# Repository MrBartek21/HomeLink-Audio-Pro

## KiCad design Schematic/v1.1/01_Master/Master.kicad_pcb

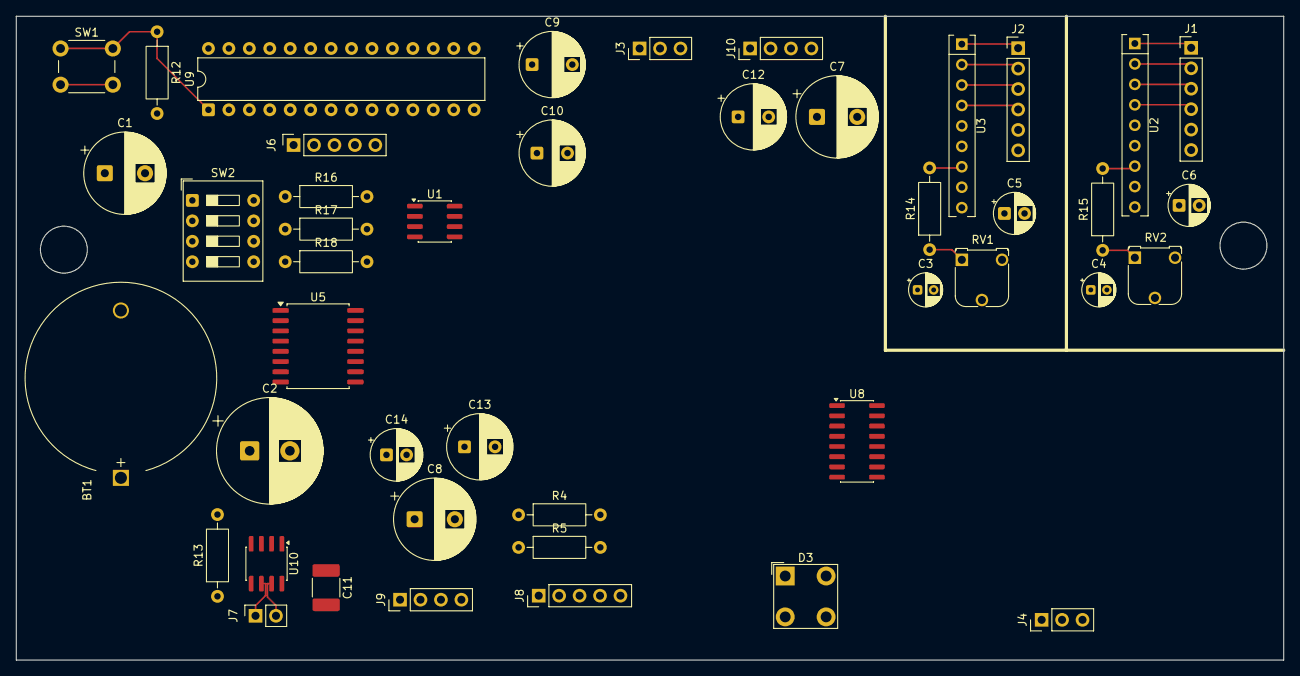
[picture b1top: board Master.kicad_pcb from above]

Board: 2 copper layers, 157.5 x 80.0 mm, 45 parts (0 on the bottom side), 40 nets.

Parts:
BT1: Battery; BatteryHolder_MYOUNG_BS-07-A1BJ001_CR2032
C1: 6.3v 3300uF; CP_Radial_D10.0mm_P5.00mm
C2: 35v 1000uF; CP_Radial_D13.0mm_P5.00mm
C3, C4: 16V 2.2uF; CP_Radial_D4.0mm_P2.00mm
C5, C6: 16V 10uF; CP_Radial_D5.0mm_P2.50mm
C7, C8: 6.3V 1500uF; CP_Radial_D10.0mm_P5.00mm
C9: 6.3V 1800uF; CP_Radial_D8.0mm_P5.00mm
C10: 6.3V 220uF; CP_Radial_D8.0mm_P3.80mm
C11: 100nF; C_1812_4532Metric_Pad1.57x3.40mm_HandSolder
C12: 10V 1000uF; CP_Radial_D8.0mm_P3.80mm
C13: 6.3V 1000uF; CP_Radial_D8.0mm_P3.80mm
C14: 16V 100uF; CP_Radial_D6.3mm_P2.50mm
D3: LED_Dual_AAKK; LED_BL-FL7680RGB
J1, J2: Conn_01x06_Pin; PinHeader_1x06_P2.54mm_Vertical
J3: BTN/LED; PinHeader_1x03_P2.54mm_Vertical
J4: AUDIO; PinHeader_1x03_P2.54mm_Vertical
J6: ISP; PinSocket_1x05_P2.54mm_Vertical
J7: RS-485; PinSocket_1x02_P2.54mm_Vertical
J8: IO/I2C; PinHeader_1x05_P2.54mm_Vertical
J9: POWER; PinHeader_1x04_P2.54mm_Vertical
J10: I2C; PinHeader_1x04_P2.54mm_Vertical
R4, R5: 4.7K; R_Axial_DIN0207_L6.3mm_D2.5mm_P10.16mm_Horizontal
R12, R14, R15: 10K; R_Axial_DIN0207_L6.3mm_D2.5mm_P10.16mm_Horizontal
R13: 5.1K; R_Axial_DIN0207_L6.3mm_D2.5mm_P10.16mm_Horizontal
R16, R17, R18: 1K; R_Axial_DIN0207_L6.3mm_D2.5mm_P10.16mm_Horizontal
RV1, RV2: 10K; Potentiometer_Runtron_RM-065_Vertical
SW1: SW_Push; SW_PUSH_6mm
SW2: SW_DIP_x04; SW_DIP_SPSTx04_Slide_9.78x12.34mm_W7.62mm_P2.54mm
U1: M24C02-FMN; SOIC-8_3.9x4.9mm_P1.27mm
U2, U3: KA2284; SIP-9_22.3x3mm_P2.54mm
U5: DS3231M; SOIC-16W_7.5x10.3mm_P1.27mm
U8: CH340C; SOIC-16_3.9x9.9mm_P1.27mm
U9: ATmega328-P; DIP-28_W7.62mm
U10: MAX485E; SOIC-8_3.9x4.9mm_P1.27mm

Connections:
+5V: C1.1, C2.1, C8.1, C9.1, C10.1, C11.1, C13.1, C14.1, J1.6, J2.6, J9.3, R4.1, R5.1, R12.2, R15.1, RV2.1, SW2.1, SW2.2, SW2.3, SW2.4, U1.8 (VCC), U2.9 (VCC), U3.9 (VCC), U5.2 (VCC), U9.7 (VCC), U9.20 (AVCC), U10.8 (VCC)
/Master/MISO: J6.4, U9.18 (PB4)
/Master/MOSI: J6.3, U9.17 (PB3)
/Master/SCK: J6.5, U9.19 (PB5)
/MultiMax/RS485-A-P: J7.1, U10.6 (A)
/MultiMax/RS485-B-N: J7.2, U10.7 (B)
ACS: J8.1, U9.23 (PC0)
ACTIVITY_ATMEGA8: D3.1 (A1), J8.2
ACTIVITY_ATMEGA328: D3.2 (A2), U9.6 (PD4)
AUDIO_L: C3.2, J4.1
AUDIO_R: C4.2, J4.3
DE_RE: R13.2, U9.14 (PB0), U10.2 (~RE), U10.3 (DE)
GND: BT1.2 (-), C1.2, C2.2, C5.2, C6.2, C7.2, C8.2, C9.2, C10.2, C11.2, C12.2, C13.2, C14.2, D3.3 (K1), D3.4 (K2), J4.2, J6.1, J8.3, J9.1, J9.2, J10.1, R13.1, R14.1, R16.1, R17.1, R18.1, RV1.1, SW1.2, U1.4 (VSS), U2.5 (GND), U3.5 (GND), U5.5 (GND), U5.6 (GND), U5.7 (GND), U5.8 (GND), U5.9 (GND), U5.10 (GND), U5.11 (GND), U5.12 (GND), U5.13 (GND), U9.8 (GND), U9.22 (GND), U10.5 (GND)
unnamed: BT1.1 (+), U5.14 (VBAT)
unnamed: C3.1, RV1.3
unnamed: C4.1, RV2.3
unnamed: J1.1, U2.1 (D1)
unnamed: J1.2, U2.2 (D2)
unnamed: J1.3, U2.3 (D3)
unnamed: J1.4, U2.4 (D4)
unnamed: J1.5, U2.6 (D5)
unnamed: J2.1, U3.1 (D1)
unnamed: J2.2, U3.2 (D2)
unnamed: J2.3, U3.3 (D3)
unnamed: J2.4, U3.4 (D4)
unnamed: J2.5, U3.6 (D5)
unnamed: C7.1, C12.1, J9.4, J10.2
unnamed: R16.2, SW2.8, U1.1 (E0)
unnamed: R17.2, SW2.7, U1.2 (E1)
unnamed: R18.2, SW2.6, U1.3 (E2)
unnamed: RV2.2, U2.8 (INPUT)
unnamed: C6.1, R15.2, U2.7 (OUT)
unnamed: RV1.2, U3.8 (INPUT)
unnamed: C5.1, R14.2, U3.7 (OUT)
RESET_ATMEGA328P: J6.2, R12.1, SW1.1, U9.1 (~RESET/PC6)
RX: U8.3 (RXD), U9.2 (PD0), U10.1 (RO)
SCL: J8.5, J10.4, R5.2, U1.6 (SCL), U5.16 (SCL), U9.28 (PC5)
SDA: J8.4, J10.3, R4.2, U1.5 (SDA), U5.15 (SDA), U9.27 (PC4)
TX: U8.2 (TXD), U9.3 (PD1), U10.4 (DI)
W_Prot: U1.7 (~WC), U9.15 (PB1)

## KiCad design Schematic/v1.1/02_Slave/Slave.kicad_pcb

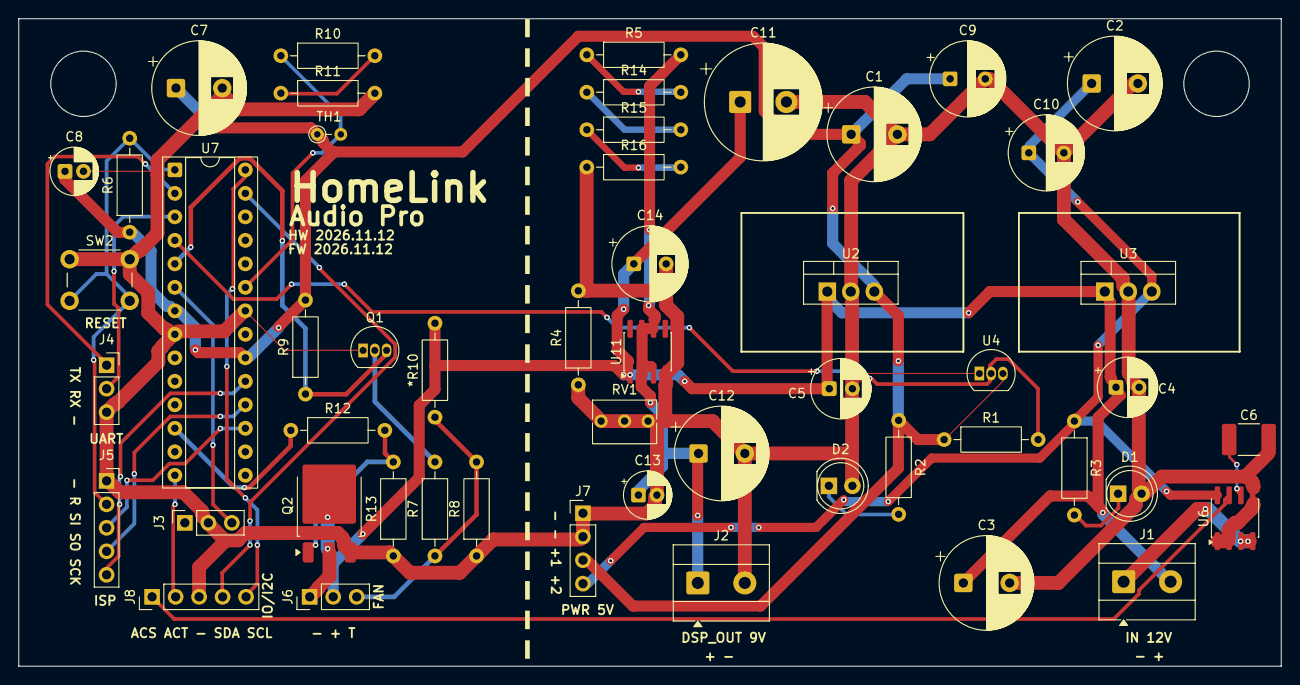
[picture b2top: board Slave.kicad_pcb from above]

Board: 2 copper layers, 136.5 x 70.0 mm, 52 parts (0 on the bottom side), 32 nets.

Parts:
*R10: *5.1K; R_Axial_DIN0207_L6.3mm_D2.5mm_P10.16mm_Horizontal
C1, C2: 6.3V 3300uF; CP_Radial_D10.0mm_P5.00mm
C3: 16v 1000uF; CP_Radial_D10.0mm_P5.00mm
C4, C5: 35v 100uF; CP_Radial_D6.3mm_P2.50mm
C6: 1nF; C_1812_4532Metric_Pad1.57x3.40mm_HandSolder
C7: 6.3v 1500uF; CP_Radial_D10.0mm_P5.00mm
C8: 16v 100uF; CP_Radial_D5.0mm_P2.00mm
C9, C10: 6.3V 1800uF; CP_Radial_D8.0mm_P3.80mm
C11: 25V 1000uF; CP_Radial_D12.5mm_P5.00mm
C12: 16V 1500uF; CP_Radial_D10.0mm_P5.00mm
C13: 16V 22uF; CP_Radial_D5.0mm_P2.00mm
C14: 450V 4.7uF; CP_Radial_D8.0mm_P3.50mm
D1, D2: LED; LED_D5.0mm
J1: 12V_IN; TerminalBlock_MetzConnect_Type101_RT01602HBWC_1x02_P5.08mm_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
J2: DSP_OUT; TerminalBlock_MetzConnect_Type101_RT01602HBWC_1x02_P5.08mm_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
J3: TACHO; PinSocket_1x03_P2.54mm_Vertical
J4: UART; PinSocket_1x03_P2.54mm_Vertical
J5: ISP; PinSocket_1x05_P2.54mm_Vertical
J6: FAN; PinHeader_1x03_P2.54mm_Vertical
J7: POWER; PinHeader_1x04_P2.54mm_Vertical
J8: IO/I2C; PinHeader_1x05_P2.54mm_Vertical
Q1: 2N3904; TO-92_Inline
Q2: Q_NMOS_GDS; TO-252-3_TabPin2
R1, R2, R3, R12: 1K; R_Axial_DIN0207_L6.3mm_D2.5mm_P10.16mm_Horizontal
R4: 1.75K; R_Axial_DIN0207_L6.3mm_D2.5mm_P10.16mm_Horizontal
R5: 200; R_Axial_DIN0207_L6.3mm_D2.5mm_P10.16mm_Horizontal
R6: 10K; R_Axial_DIN0207_L6.3mm_D2.5mm_P10.16mm_Horizontal
R7, R10, R11, R13: 5.1K; R_Axial_DIN0207_L6.3mm_D2.5mm_P10.16mm_Horizontal
R8, R9: 4.7K; R_Axial_DIN0207_L6.3mm_D2.5mm_P10.16mm_Horizontal
R14, R15, R16: 15; R_Axial_DIN0207_L6.3mm_D2.5mm_P10.16mm_Horizontal
RV1: 20K; Potentiometer_Bourns_3266Y_Vertical
SW2: RESET; SW_PUSH_6mm
TH1: Thermistor_NTC; R_Axial_DIN0204_L3.6mm_D1.6mm_P2.54mm_Vertical
U2, U3: L7805; TO-220-3_Vertical
U4: DS18B20; TO-92_Inline
U6: ACS712xLCTR-30A; SOIC-8_3.9x4.9mm_P1.27mm
U7: ATmega8-16P; DIP-28_W7.62mm_Socket
U11: LM317L_SO8; SOIC-8_3.9x4.9mm_P1.27mm

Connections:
+5V: C1.1, C7.1, C8.1, C9.1, J7.3, R1.1, R2.1, R6.1, R9.2, TH1.1, U2.3 (OUT), U4.3 (V_{DD}), U7.7 (VCC), U7.20 (AVCC)
+12V: *R10.2, C3.1, C4.1, C5.1, C11.1, C14.1, J1.2, J6.2, U2.1 (IN), U3.1 (IN), U11.1 (VI)
/Slave/MISO: J5.4, U7.18 (PB4)
/Slave/MOSI: J5.3, U7.17 (PB3)
/Slave/RESET: J5.2, R6.2, SW2.2, U7.1 (PC6/~RESET)
/Slave/RX: J4.2, U7.3 (PD1)
/Slave/SCK: J5.5, U7.19 (PB5)
/Slave/TX: J4.1, U7.2 (PD0)
ACS_OUT: J8.1, U6.7 (VIOUT)
ACTIVITY_OUT: J8.2, U7.14 (PB0)
DQ: R1.2, U4.2 (DQ), U7.4 (PD2)
FAN_M: J6.1, Q2.2 (D)
GND: C1.2, C2.2, C3.2, C4.2, C5.2, C6.2, C7.2, C8.2, C9.2, C10.2, C11.2, C12.2, C13.2, C14.2, D1.2 (A), D2.2 (A), J2.2, J3.2, J4.3, J5.1, J7.1, J7.2, J8.3, Q1.1 (E), Q2.3 (S), R4.1, R4.2, R8.1, R11.2, R13.1, R16.1, RV1.1, RV1.2, RV1.3, SW2.1, U2.2 (GND), U3.2 (GND), U4.1 (GND), U6.1 (IP+), U6.2 (IP+), U6.5 (GND), U7.8 (GND), U7.22 (AGND), U11.4 (ADJ)
NTC: R10.1, TH1.2, U7.23 (PC0)
unnamed: D1.1 (K), R3.2
unnamed: D2.1 (K), R2.2
unnamed: J1.1, U6.3 (IP-), U6.4 (IP-)
unnamed: C12.1, C13.1, J2.1, R5.2, U11.2 (VO), U11.3 (VO), U11.6 (VO), U11.7 (VO)
unnamed: J3.3, U7.6 (PD4)
unnamed: C2.1, C10.1, J7.4, R3.1, U3.3 (OUT), U6.8 (VCC)
unnamed: Q1.2 (B), R7.2
unnamed: Q2.1 (G), R12.2, R13.2
unnamed: R10.2, R11.1
unnamed: R14.1, R15.2
unnamed: R5.1, R14.2
unnamed: R15.1, R16.2
unnamed: C6.1, U6.6 (FILTER)
RLY2: R12.1, U7.12 (PD6)
SCL_OUT: J8.5, U7.28 (PC5)
SDA_OUT: J8.4, U7.27 (PC4)
TACHO: Q1.3 (C), R9.1, U7.5 (PD3)
TACHO_FAN: *R10.1, J6.3, R7.1, R8.2

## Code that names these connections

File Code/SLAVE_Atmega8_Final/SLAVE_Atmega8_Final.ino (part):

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#include <math.h>

// HomeLink Audio Pro - ATmega8 final slave
// PC0 NTC, PC4/PC5 I2C slave, PD2 DS18B20, PD5 RLY1, PD6 RLY2, PB0 LED.
// PD0/PD1 are diagnostic UART at 9600 baud. No external crystal.

#define I2C_ADDRESS          0x12
#define DS18B20_BIT          PD2
#define TACHO_BIT            PD3
#define TACHO_MODE_BIT       PD4
#define RELAY1_BIT           PD5
#define RELAY2_BIT           PD6
#define ACTIVITY_LED_BIT     PB0
#define RELAY_ACTIVE_LOW     1

// Divider: +5V -> NTC -> PC0 -> 10k -> GND.
#define NTC_FIXED_OHMS       10000.0f
#define NTC_NOMINAL_OHMS     47000.0f
#define NTC_NOMINAL_C        25.0f
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
static uint16_t readAdc0()
{
    ADMUX = _BV(REFS0); // AVCC reference, ADC0/PC0
    ADCSRA = _BV(ADEN) | _BV(ADPS2) | _BV(ADPS1) | _BV(ADPS0);
    delayMicroseconds(100);
    ADCSRA |= _BV(ADSC);
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    Wire.onRequest(onRequest);

    tachoEnabled = (PIND & _BV(TACHO_MODE_BIT)) == 0;
    // INT1 / PD3, falling edge. The transistor output is pulled up to +5 V.
    // ATmega8 uses MCUCR/GICR, unlike newer AVR devices using EICRA/EIMSK.
    MCUCR = (MCUCR & (uint8_t)~(_BV(ISC11) | _BV(ISC10))) | _BV(ISC11);
    GICR |= _BV(INT1);
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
